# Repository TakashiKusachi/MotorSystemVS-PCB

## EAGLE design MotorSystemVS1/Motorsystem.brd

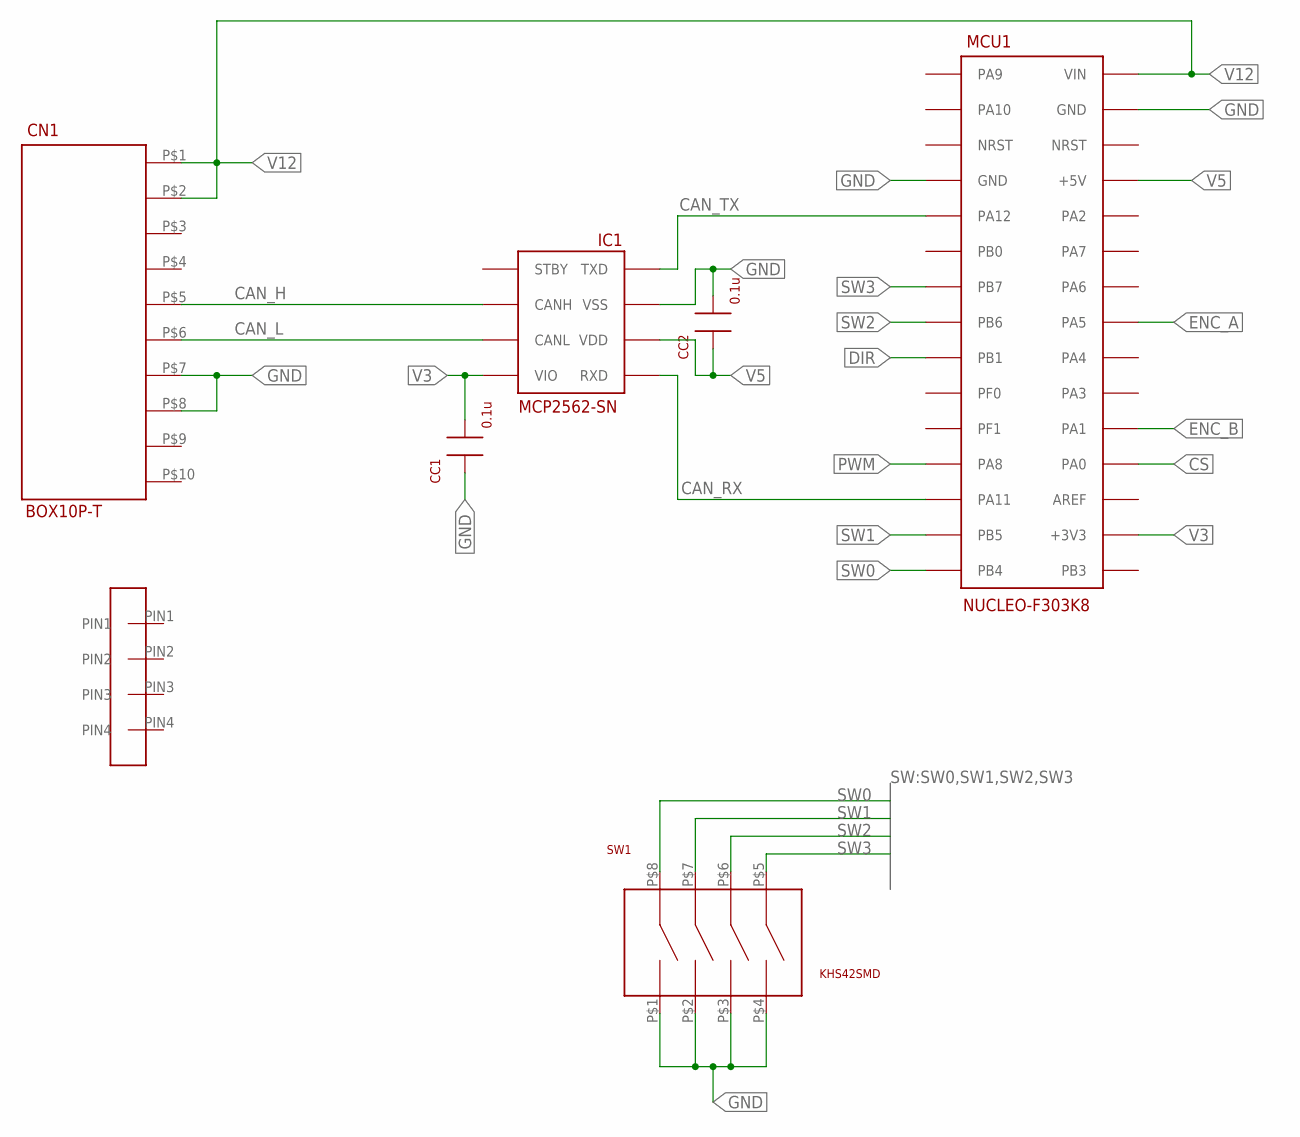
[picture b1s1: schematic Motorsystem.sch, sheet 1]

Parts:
CC1, CC2: 0.1u; C1608
CN1: BOX10P-T
IC1: MCP2562-SN; SOIC8
MCU1: NUCLEO-F303K8; NUCLEO-NANO
SW1: KHS42SMD; KHS42
U$3: DF1B_L_4P

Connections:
CAN_H: CN1.P$5, IC1.P$7 (CANH)
CAN_L: CN1.P$6, IC1.P$6 (CANL)
CAN_RX: IC1.P$4 (RXD), MCU1.P$13 (PA11)
CAN_TX: IC1.P$1 (TXD), MCU1.P$5 (PA12)
CS: MCU1.P$19 (PA0)
DIR: MCU1.P$9 (PB1)
ENC_A: MCU1.P$23 (PA5)
ENC_B: MCU1.P$20 (PA1)
GND: CC1.P$1, CC2.P$2, CN1.P$7, CN1.P$8, IC1.P$2 (VSS), MCU1.P$4 (GND), MCU1.P$29 (GND), SW1.P$1, SW1.P$2, SW1.P$3, SW1.P$4; also elsewhere on the board
PWM: MCU1.P$12 (PA8); also elsewhere on the board
SW0: MCU1.P$15 (PB4), SW1.P$8
SW1: MCU1.P$14 (PB5), SW1.P$7
SW2: MCU1.P$8 (PB6), SW1.P$6
SW3: MCU1.P$7 (PB7), SW1.P$5
V3: CC1.P$2, IC1.P$5 (VIO), MCU1.P$17 (+3V3)
V5: CC2.P$1, IC1.P$3 (VDD), MCU1.P$27 (+5V)
V12: CN1.P$1, CN1.P$2, MCU1.P$30 (VIN)

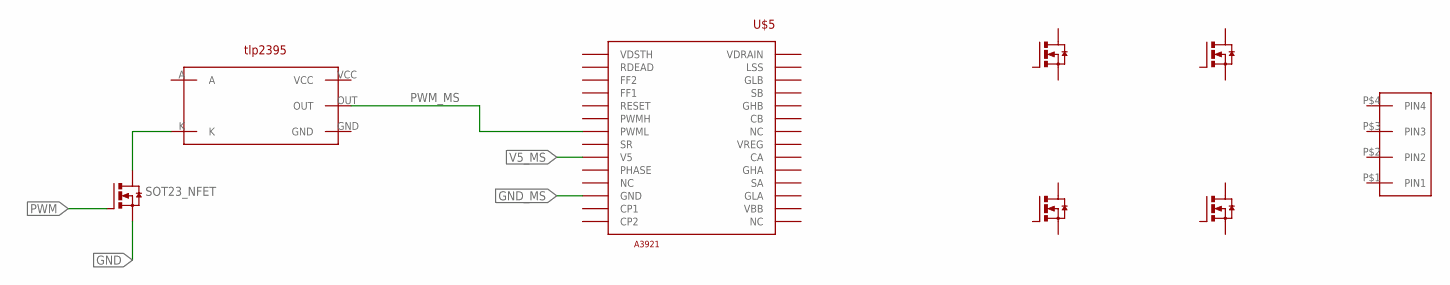
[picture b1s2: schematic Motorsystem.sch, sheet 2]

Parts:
U$1: TLP2395
U$2: SOT23_NFET
U$4, U$6, U$7, U$8: NP52N06SLG
U$5: A3921
U$9: VL_4P

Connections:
GND: U$2.PIN2_S; also elsewhere on the board
GND_MS: U$5.PAD (GND), U$5.PIN17 (GND)
unnamed: U$1.K, U$2.PIN3_D
PWM: U$2.PIN1_G; also elsewhere on the board
PWM_MS: U$1.OUT, U$5.PIN22 (PWML)
V5_MS: U$5.PIN20 (V5)

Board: 2 copper layers, 15 parts (5 on the bottom side), 16 nets, no tracks yet.

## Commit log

2020-10-07 init commit
2020-10-08 continue
2020-11-01 add dir
